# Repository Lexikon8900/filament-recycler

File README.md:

# filament-recycler
Mechanics and electronics for a fully functual filament melter, wich isn`t exspensive.(granulate melting)

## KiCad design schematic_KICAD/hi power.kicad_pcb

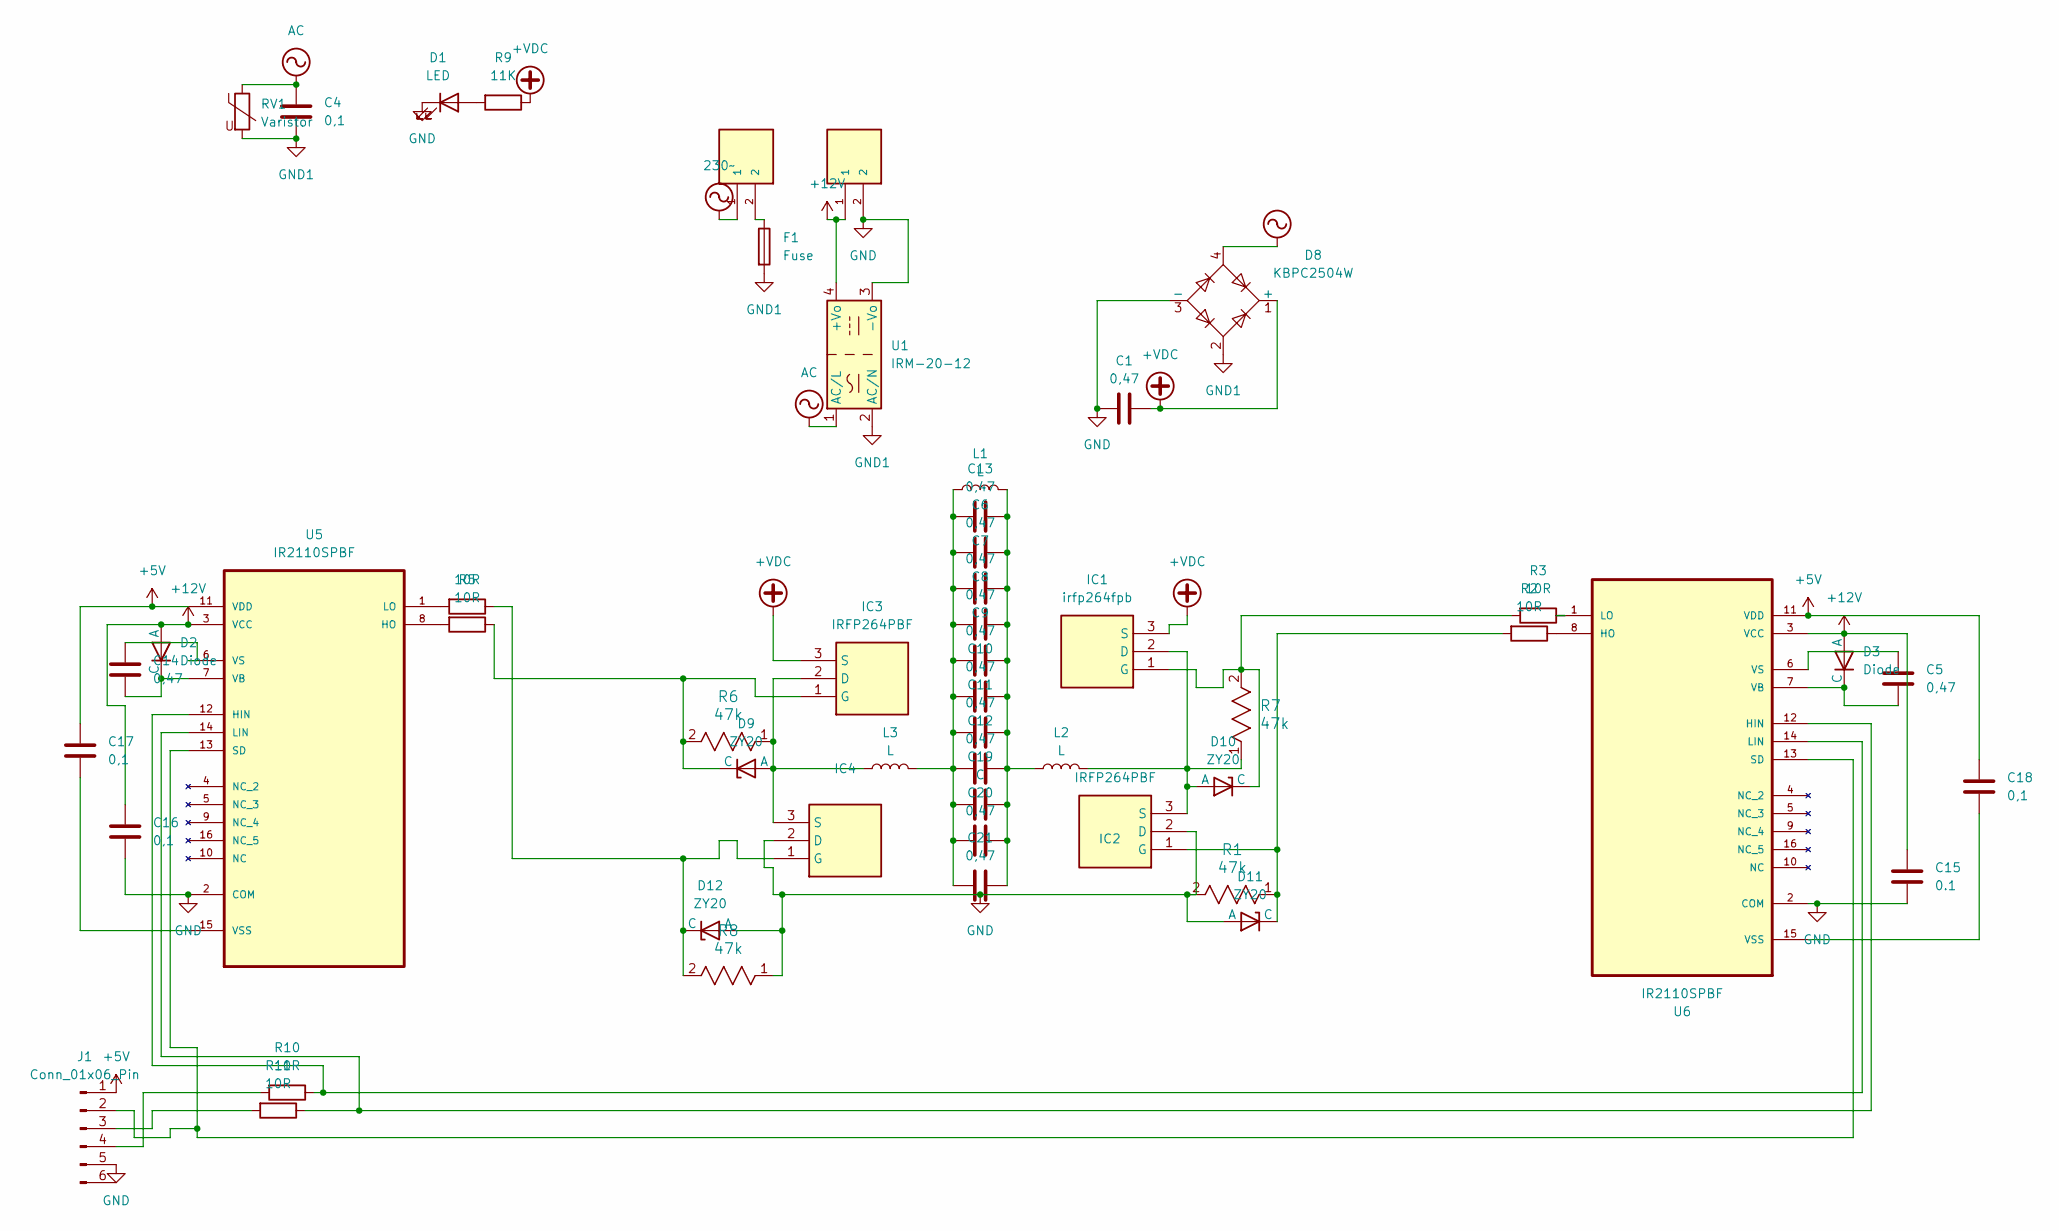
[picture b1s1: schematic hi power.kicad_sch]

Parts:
C1, C6, C7, C8, C9, C10, C11, C12, C13, C20, C21: 0,47; CAP_R463N347000N0M_KEM
C4: 0,1; C_Axial_L3.8mm_D2.6mm_P10.00mm_Horizontal
C5, C14: 0,47; CP_Radial_D8.0mm_P3.50mm
C15: 0.1; C_0805_2012Metric_Pad1.18x1.45mm_HandSolder
C16, C17, C18: 0,1; C_0805_2012Metric_Pad1.18x1.45mm_HandSolder
C19: C; CAP_R463N347000N0M_KEM
D1: LED; LED_D5.0mm_FlatTop
D2, D3: Diode; P1_DO-41
D8: KBPC2504W; Diode_Bridge_DIGITRON_KBPC_T
D9, D10, D11, D12: ZY20; P1_DO-41
F1: Fuse; Fuse_Littelfuse-LVR100
IC1: irfp264fpb; TO-247AC_VIS; Mouser Part Number 844-IRFP264PBF
IC2, IC3: IRFP264PBF; TO-247AC_VIS; Mouser Part Number 844-IRFP264PBF
IC4: TO-247AC_VIS; Mouser Part Number 844-IRFP264PBF
J1: Conn_01x06_Pin; TE_826576-6_1x06_P3.96mm_Vertical
J2, J3: 282841-2; TE_282841-2; PARTREV H6
L1: L
L2, L3: L; torodial inductor
R1, R6, R7, R8: 47k; RES_ROX3S_TYCO_TYC
R2, R3, R4, R5: 10R; R_1206_3216Metric_Pad1.30x1.75mm_HandSolder
R9: 11K; R_Axial_DIN0411_L9.9mm_D3.6mm_P12.70mm_Horizontal
R10, R11: 10R; C_Axial_L5.1mm_D3.1mm_P12.50mm_Horizontal
RV1: Varistor; VRES_B77214_EPC
U1: IRM-20-12; Converter_ACDC_MeanWell_IRM-20-xx_THT
U5, U6: IR2110SPBF; SOIC127P1030X265-16N; MPN IR2110SPBF

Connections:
230~: J3.1
+5V: C17.1, C18.1, J1.1, U5.11 (VDD), U6.11 (VDD)
+12V: C15.1, C16.1, D2.1 (A), D3.1 (A), J2.1, U1.4 (+Vo), U5.3 (VCC), U6.3 (VCC)
+VDC: C1.2, D8.1 (+), IC1.3 (S), IC3.3 (S), R9.1
AC: C4.1, D8.4, RV1.1, U1.1 (AC/L)
GND: C1.1, C15.2, C16.2, D1.1 (K), D8.3 (-), D11.2 (A), D12.2 (A), IC2.2 (D), IC4.2 (D), J1.5, J2.2, R1.2, R8.1, U1.3 (-Vo), U5.2 (COM), U6.2 (COM)
GND1: C4.2, D8.2, F1.2, RV1.2, U1.2 (AC/N)
unnamed: C6.1, C7.1, C8.1, C9.1, C10.1, C11.1, C12.1, C13.1, C19.1, C20.1, C21.1, L1.1, L3.2
unnamed: C6.2, C7.2, C8.2, C9.2, C10.2, C11.2, C12.2, C13.2, C19.2, C20.2, C21.2, L1.2, L2.1
unnamed: D1.2 (A), R9.2
unnamed: C14.2, D2.2 (C), U5.7 (VB)
unnamed: C5.2, D3.2 (C), U6.7 (VB)
unnamed: D9.2 (A), IC3.2 (D), IC4.3 (S), L3.1, R6.1
unnamed: D9.1 (C), IC3.1 (G), R5.1, R6.2
unnamed: D10.2 (A), IC1.2 (D), IC2.3 (S), L2.2, R7.1
unnamed: D10.1 (C), IC1.1 (G), R3.2, R7.2
unnamed: D11.1 (C), IC2.1 (G), R1.1, R2.2
unnamed: D12.1 (C), IC4.1 (G), R4.1, R8.2
unnamed: F1.1, J3.2
unnamed: J1.2, U5.13 (SD), U6.13 (SD)
unnamed: J1.3, R11.2
unnamed: J1.4, R10.2
unnamed: R10.1, U5.12 (HIN), U6.14 (LIN)
unnamed: R5.2, U5.8 (HO)
unnamed: R11.1, U5.14 (LIN), U6.12 (HIN)
unnamed: R4.2, U5.1 (LO)
unnamed: C14.1, U5.6 (VS)
unnamed: C17.2, U5.15 (VSS)
unnamed: R2.1, U6.8 (HO)
unnamed: R3.1, U6.1 (LO)
unnamed: C5.1, U6.6 (VS)
unnamed: C18.2, U6.15 (VSS)

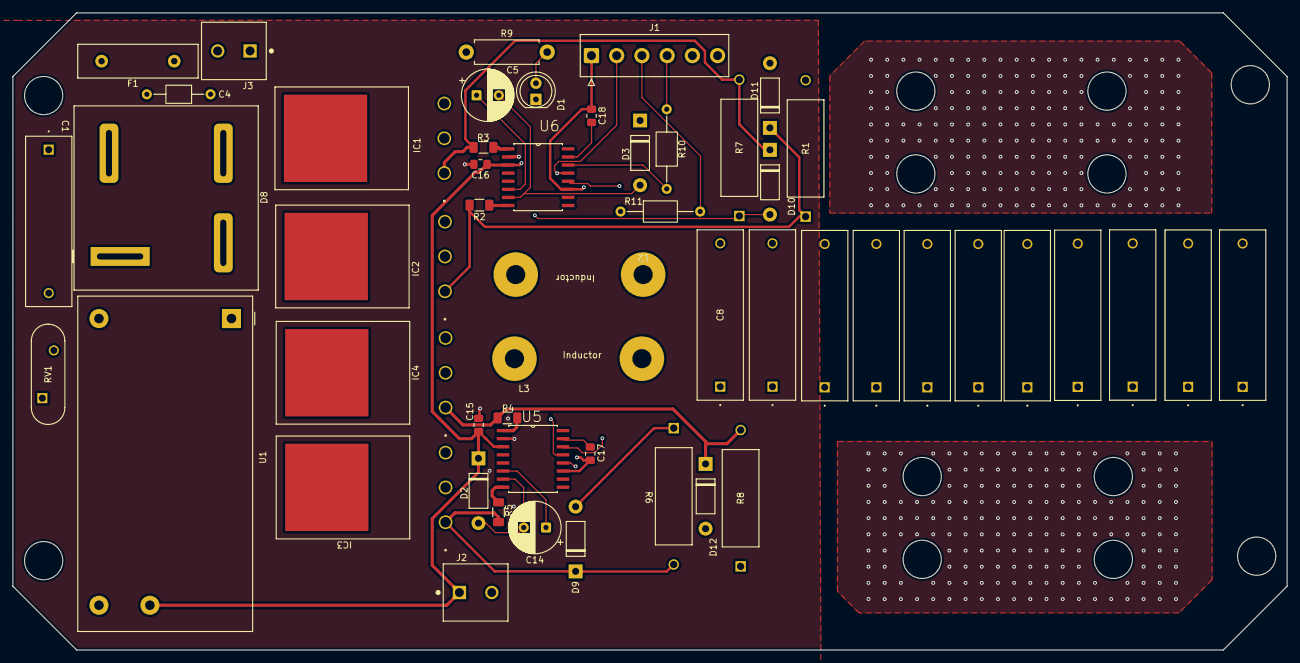
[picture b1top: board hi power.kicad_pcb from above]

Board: 4 copper layers, 200.0 x 100.0 mm, 52 parts (0 on the bottom side), 31 nets.

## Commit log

2026-06-06 adding schematics for high frequenzy induction
